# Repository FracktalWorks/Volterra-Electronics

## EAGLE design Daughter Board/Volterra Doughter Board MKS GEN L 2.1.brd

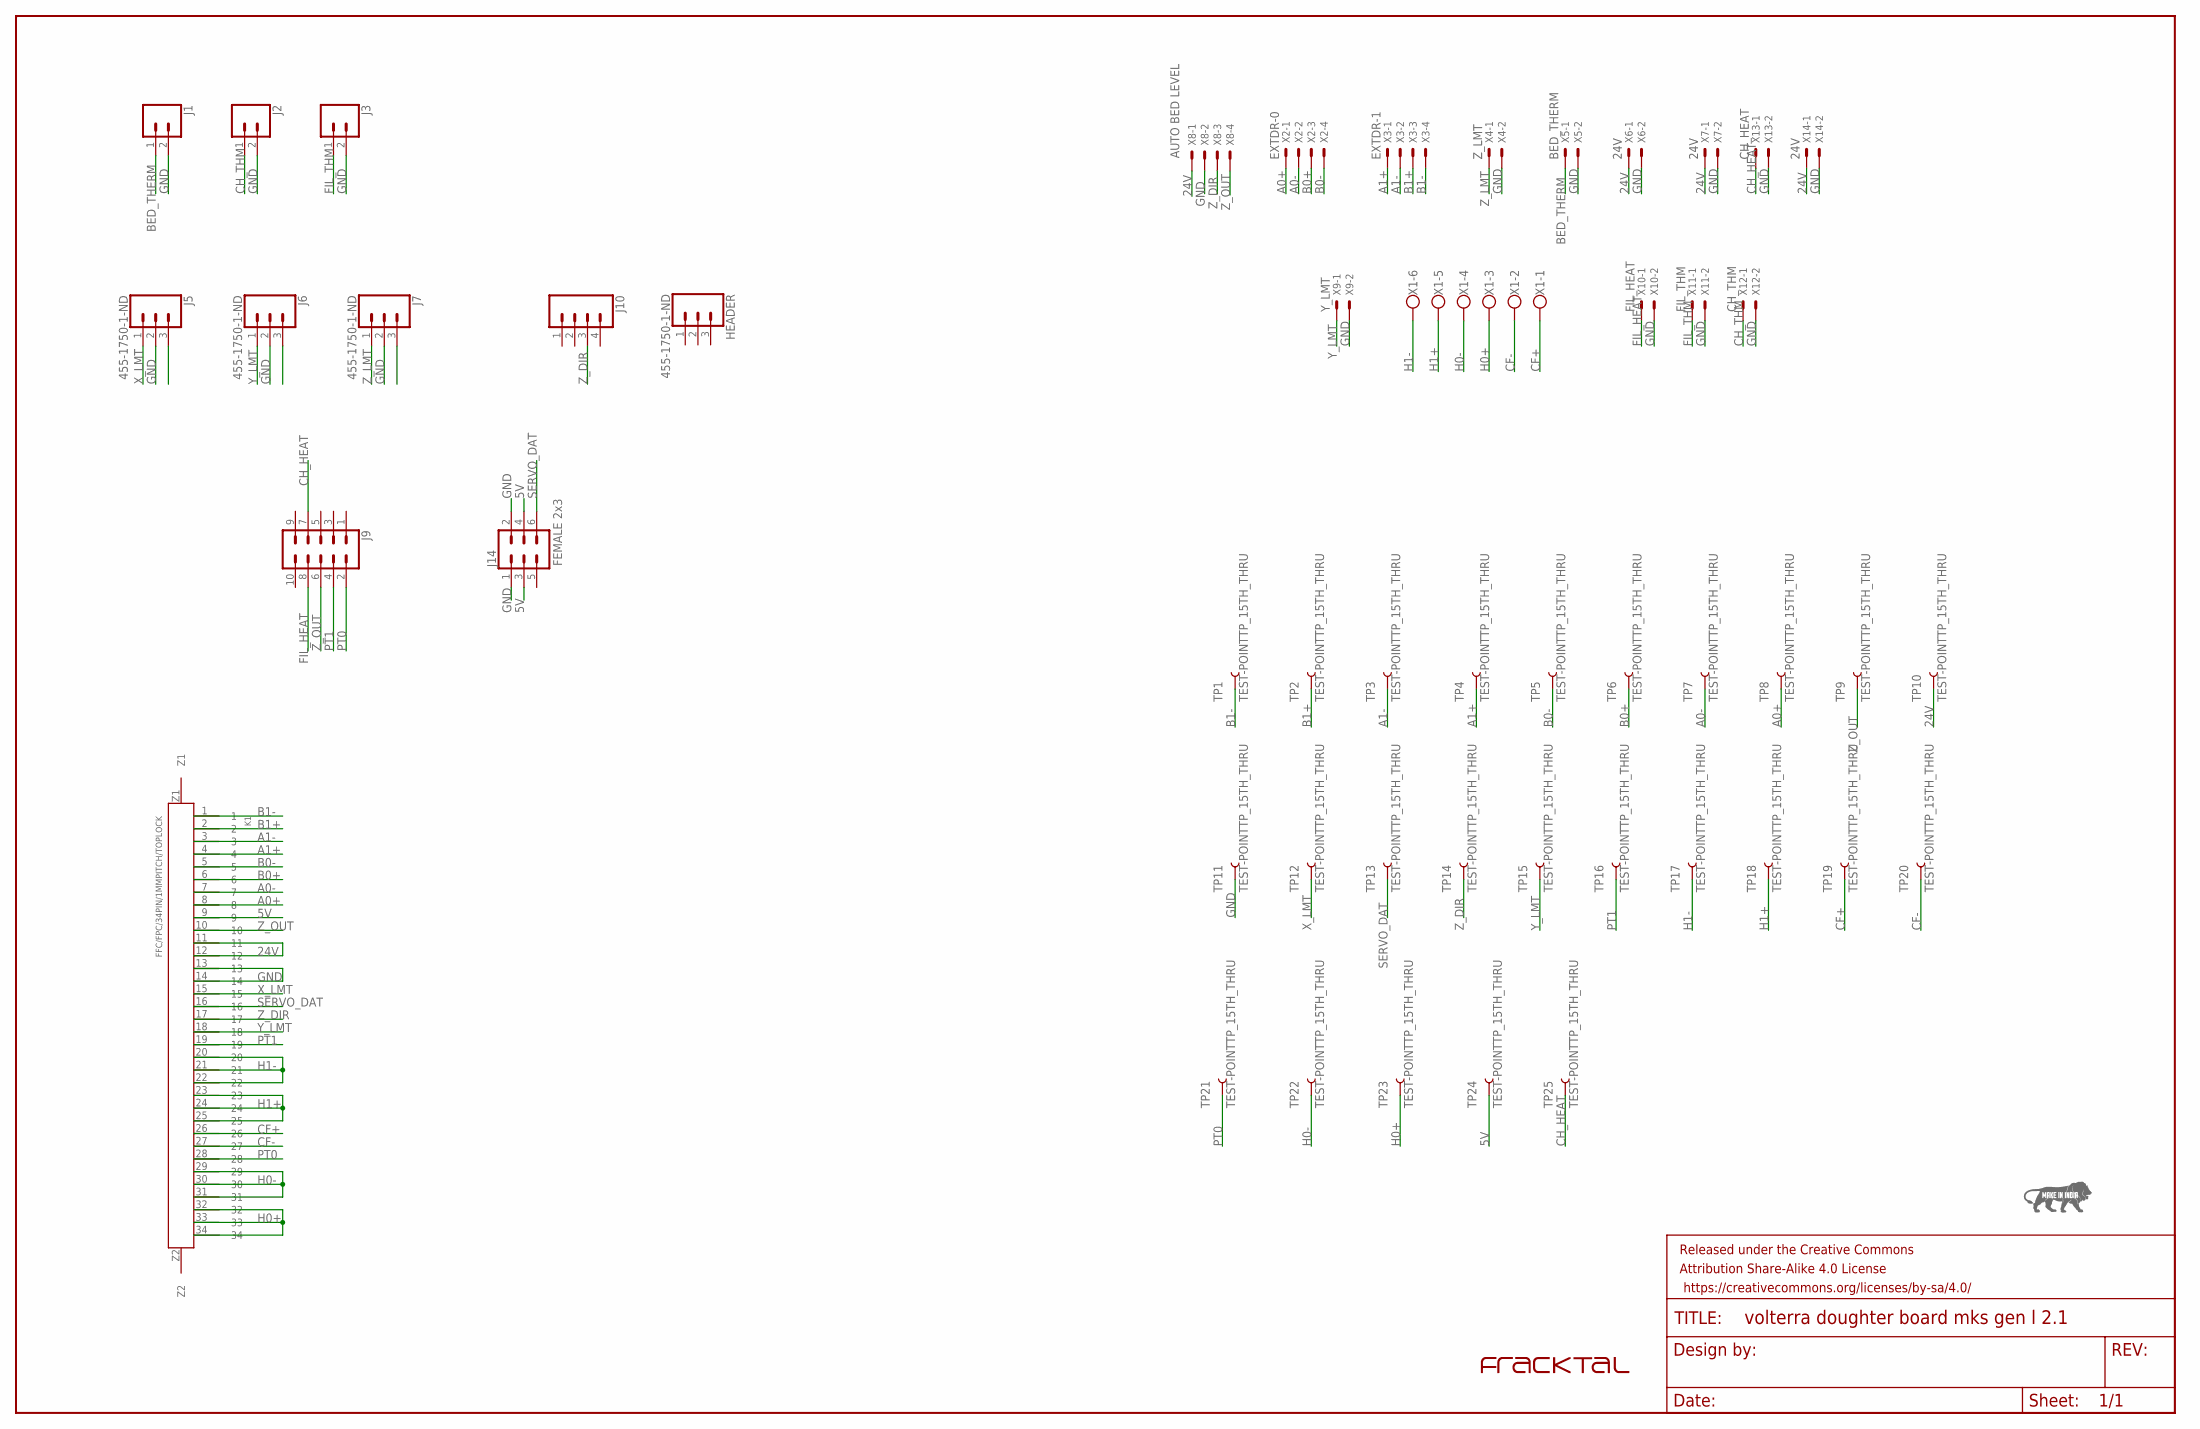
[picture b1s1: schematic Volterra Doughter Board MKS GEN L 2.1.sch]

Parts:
FRAME1: FRAME-LEDGER; CREATIVE_COMMONS
HEADER: 455-1750-1-ND; 1X03
J1, J2, J3: CONN_02; 1X02
J5, J6, J7: 455-1750-1-ND; 1X03
J9: CONN_05X2PTH; 2X5
J10: CONN_04; 1X04
J14: FEMALE 2x3; 2X3
K1: FFC/FPC/34PIN/1MMPITCH/TOPLOCK; 34PIN/1MMPITCH/FFC/FPC
TP1, TP2, TP3, TP4, TP5, TP6, TP7, TP8, TP9, TP10, TP11, TP12, TP13, TP14, TP15, TP16, TP17, TP18, TP19, TP20, TP21, TP22, TP23, TP24, TP25: TEST-POINTTP_15TH_THRU; TP_15TH
U$1: FRACKTALLOGO
U$2: MAKEININDIA
X1: W237-6
X2: EXTDR-0; JST-XH-04-PACKAGE-LONG-PAD
X3: EXTDR-1; JST-XH-04-PACKAGE-LONG-PAD
X4: Z_LMT; JST-XH-02-PACKAGE-LONG-PAD
X5: BED_THERM; JST-XH-02-PACKAGE-LONG-PAD
X6, X7, X14: 24V; JST-XH-02-PACKAGE-LONG-PAD
X8: AUTO BED LEVELING; JST-XH-04-PACKAGE-LONG-PAD
X9: Y_LMT; JST-XH-02-PACKAGE-LONG-PAD
X10: FIL_HEAT; JST-XH-02-PACKAGE-LONG-PAD
X11: FIL_THM; JST-XH-02-PACKAGE-LONG-PAD
X12: CH_THM; JST-XH-02-PACKAGE-LONG-PAD
X13: CH_HEAT; JST-XH-02-PACKAGE-LONG-PAD

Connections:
5V: J14.3, J14.4, K1.9, TP24.P$1
24V: K1.11, K1.12, TP10.P$1, X6.1, X7.1, X8.1, X14.1
A0+: K1.8, TP8.P$1, X2.1
A0-: K1.7, TP7.P$1, X2.2
A1+: K1.4, TP4.P$1, X3.1
A1-: K1.3, TP3.P$1, X3.2
B0+: K1.6, TP6.P$1, X2.3
B0-: K1.5, TP5.P$1, X2.4
B1+: K1.2, TP2.P$1, X3.3
B1-: K1.1, TP1.P$1, X3.4
BED_THERM: J1.1, X5.1
CF+: K1.26, TP19.P$1, X1.1
CF-: K1.27, TP20.P$1, X1.2
CH_HEAT: J9.7, TP25.P$1, X13.1
CH_THM: J2.1, X12.1
FIL_HEAT: J9.8, X10.1
FIL_THM: J3.1, X11.1
GND: J1.2, J2.2, J3.2, J5.2, J6.2, J7.2, J14.1, J14.2, K1.13, K1.14, TP11.P$1, X4.2, X5.2, X6.2, X7.2, X8.2, X9.2, X10.2, X11.2, X12.2, X13.2, X14.2
H0+: K1.32, K1.33, K1.34, TP23.P$1, X1.3
H0-: K1.29, K1.30, K1.31, TP22.P$1, X1.4
H1+: K1.23, K1.24, K1.25, TP18.P$1, X1.5
H1-: K1.20, K1.21, K1.22, TP17.P$1, X1.6
PT0: J9.2, K1.28, TP21.P$1
PT1: J9.4, K1.19, TP16.P$1
SERVO_DAT: J14.6, K1.16, TP13.P$1
X_LMT: J5.1, K1.15, TP12.P$1
Y_LMT: J6.1, K1.18, TP15.P$1, X9.1
Z_DIR: J10.3, K1.17, TP14.P$1, X8.3
Z_LMT: J7.1, X4.1
Z_OUT: J9.6, K1.10, TP9.P$1, X8.4

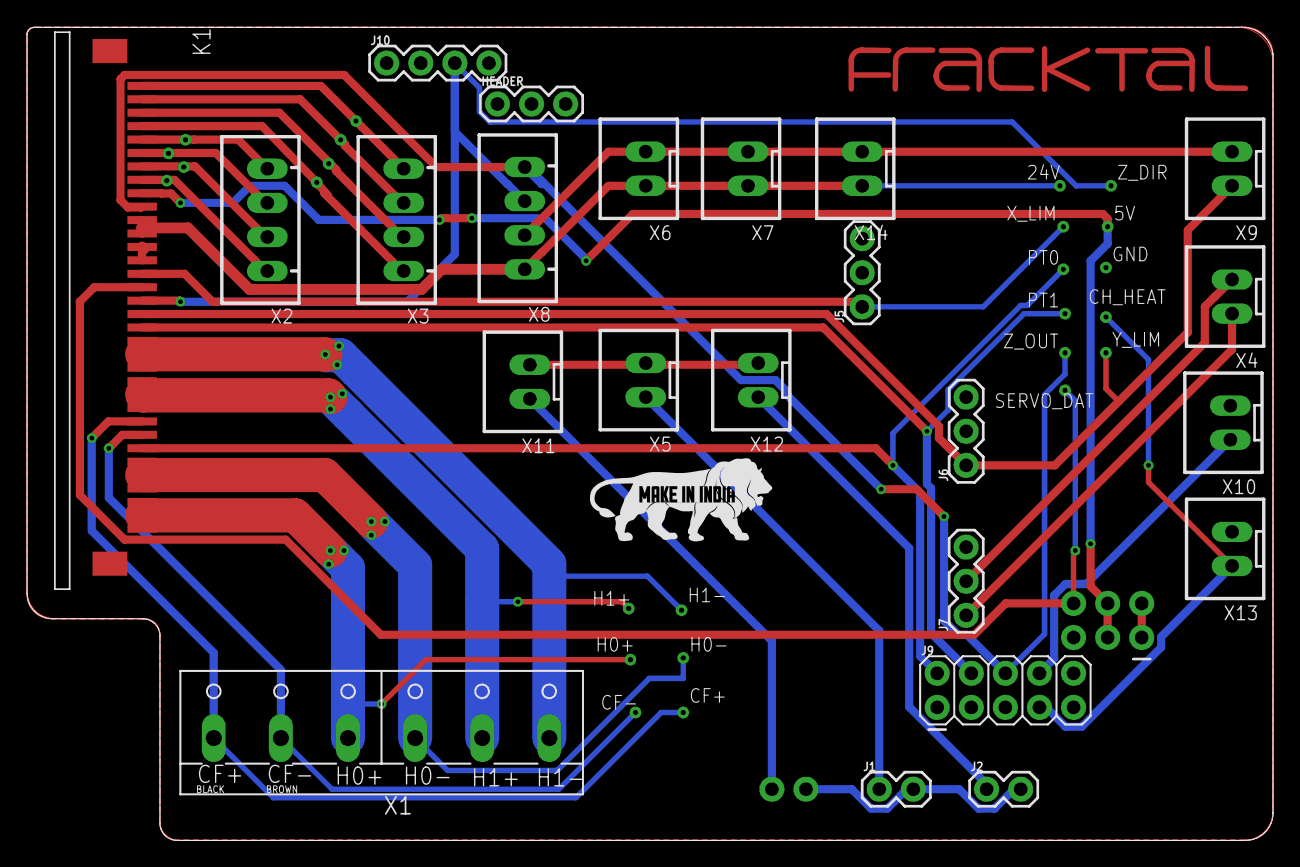
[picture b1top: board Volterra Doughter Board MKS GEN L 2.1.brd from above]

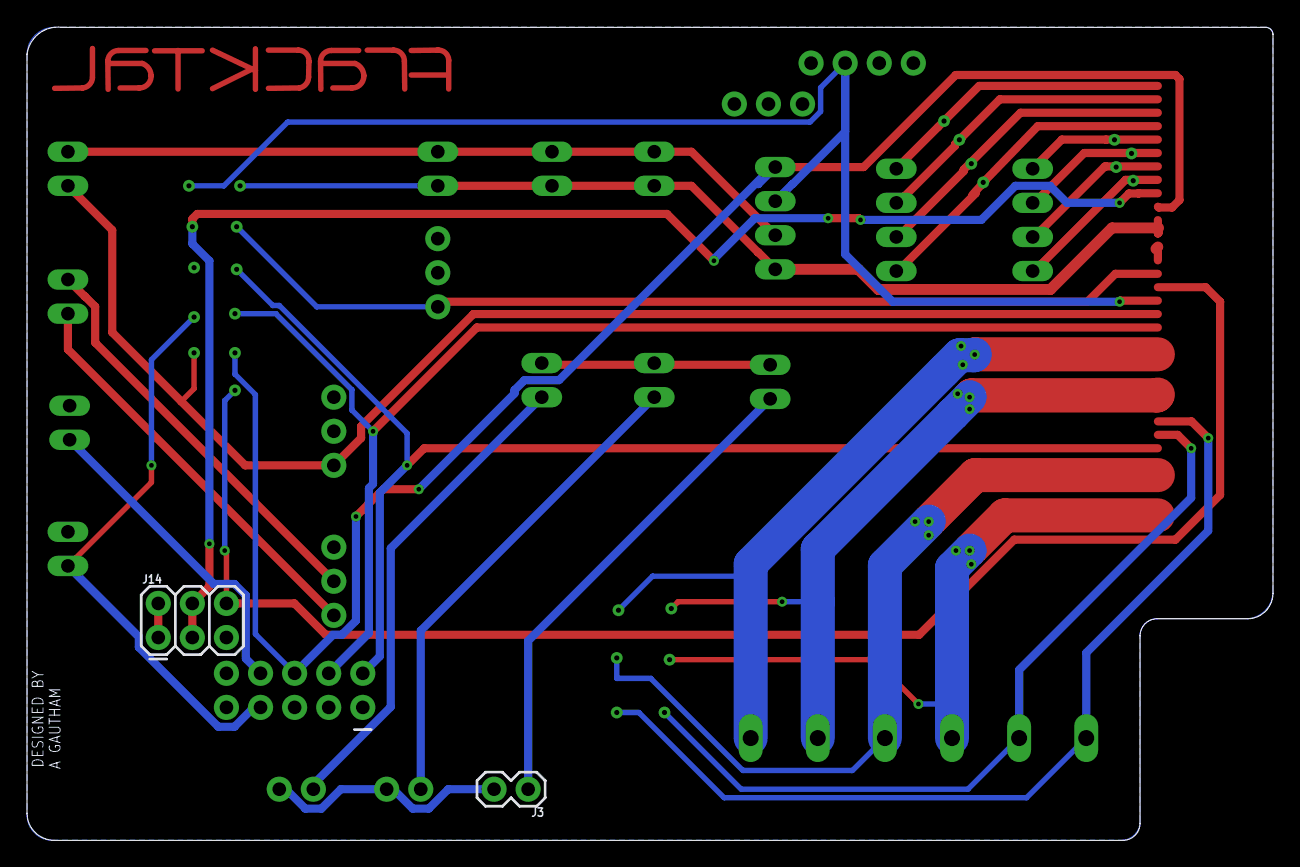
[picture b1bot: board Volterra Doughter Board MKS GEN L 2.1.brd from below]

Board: 2 copper layers, 92.8 x 60.6 mm, 53 parts (3 on the bottom side), 30 nets.

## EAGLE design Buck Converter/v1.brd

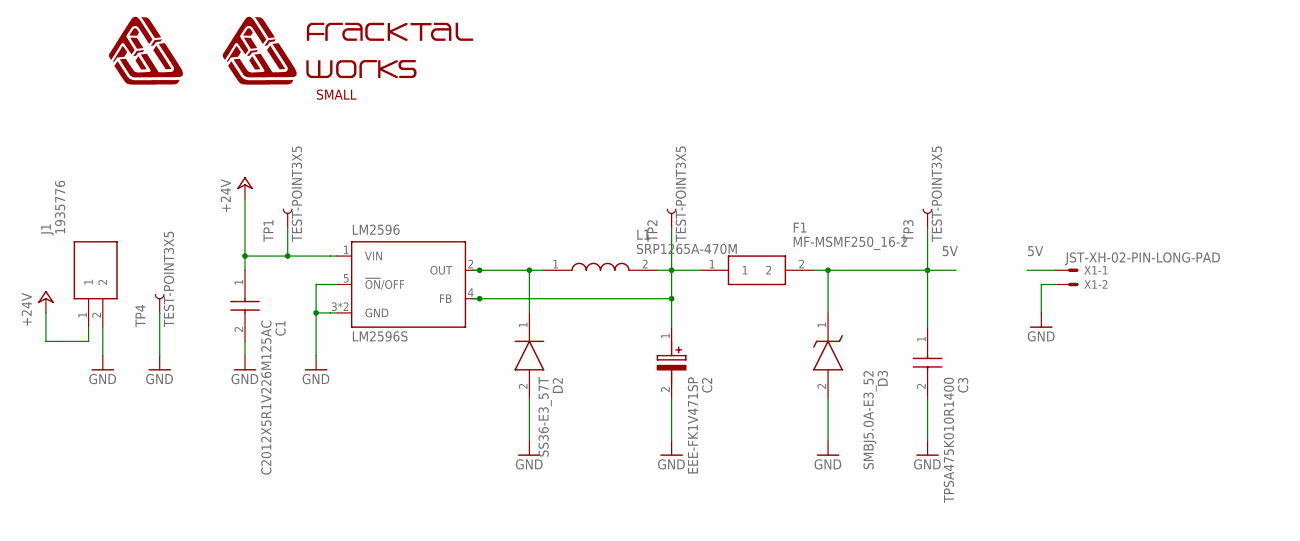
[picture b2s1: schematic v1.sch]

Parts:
C1: C2012X5R1V226M125AC; CAPC2012X145N
C2: EEE-FK1V471SP; CAPAE1030X1050N
C3: TPSA475K010R1400; CAPPM3216X180N
D2: SS36-E3_57T; DIOM7959X262N
D3: SMBJ5.0A-E3_52; DIOM5436X244N
F1: MF-MSMF250_16-2; FUSC4632X160N
J1: 1935776; SHDR2W110P0X500_1X2_1000X900X1
L1: SRP1265A-470M; SRP1265A
LM2596: LM2596S; LM2596_TO263-5
TP1, TP2, TP3, TP4: TEST-POINT3X5; PAD.03X.05
U$1: FWLOGO
U$2: FWLOGO_TEXT_SMALL
X1: JST-XH-02-PIN-LONG-PAD; JST-XH-02-PACKAGE-LONG-PAD

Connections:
5V: C3.1, D3.1 (K), F1.2, TP3.P$1, X1.1
+24V: C1.1, J1.1, LM2596.1 (VIN), TP1.P$1
GND: C1.2, C2.2 (-), C3.2, D2.2 (A), D3.2 (A), J1.2, LM2596.3 (GND), LM2596.5 (!ON!/OFF), LM2596.6 (GND), TP4.P$1, X1.2
unnamed: D2.1 (K), L1.1, LM2596.2 (OUT)
unnamed: C2.1 (+), F1.1, L1.2, LM2596.4 (FB), TP2.P$1

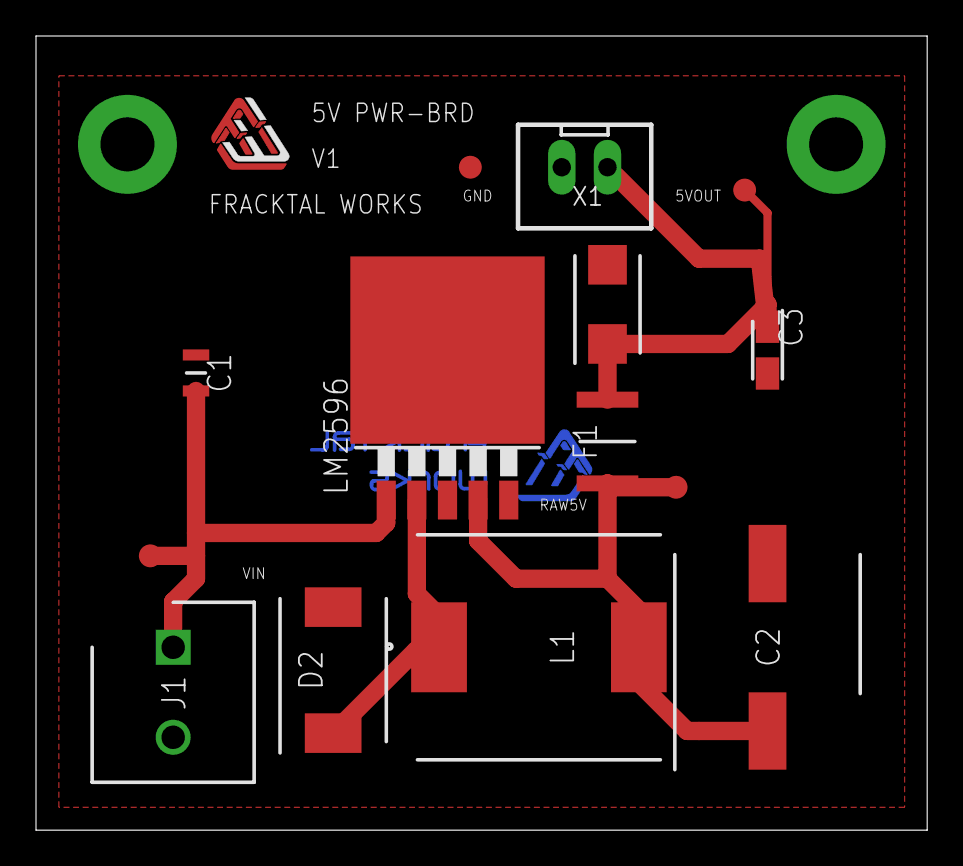
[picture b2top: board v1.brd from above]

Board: 2 copper layers, 49.5 x 44.1 mm, 16 parts (1 on the bottom side), 5 nets.

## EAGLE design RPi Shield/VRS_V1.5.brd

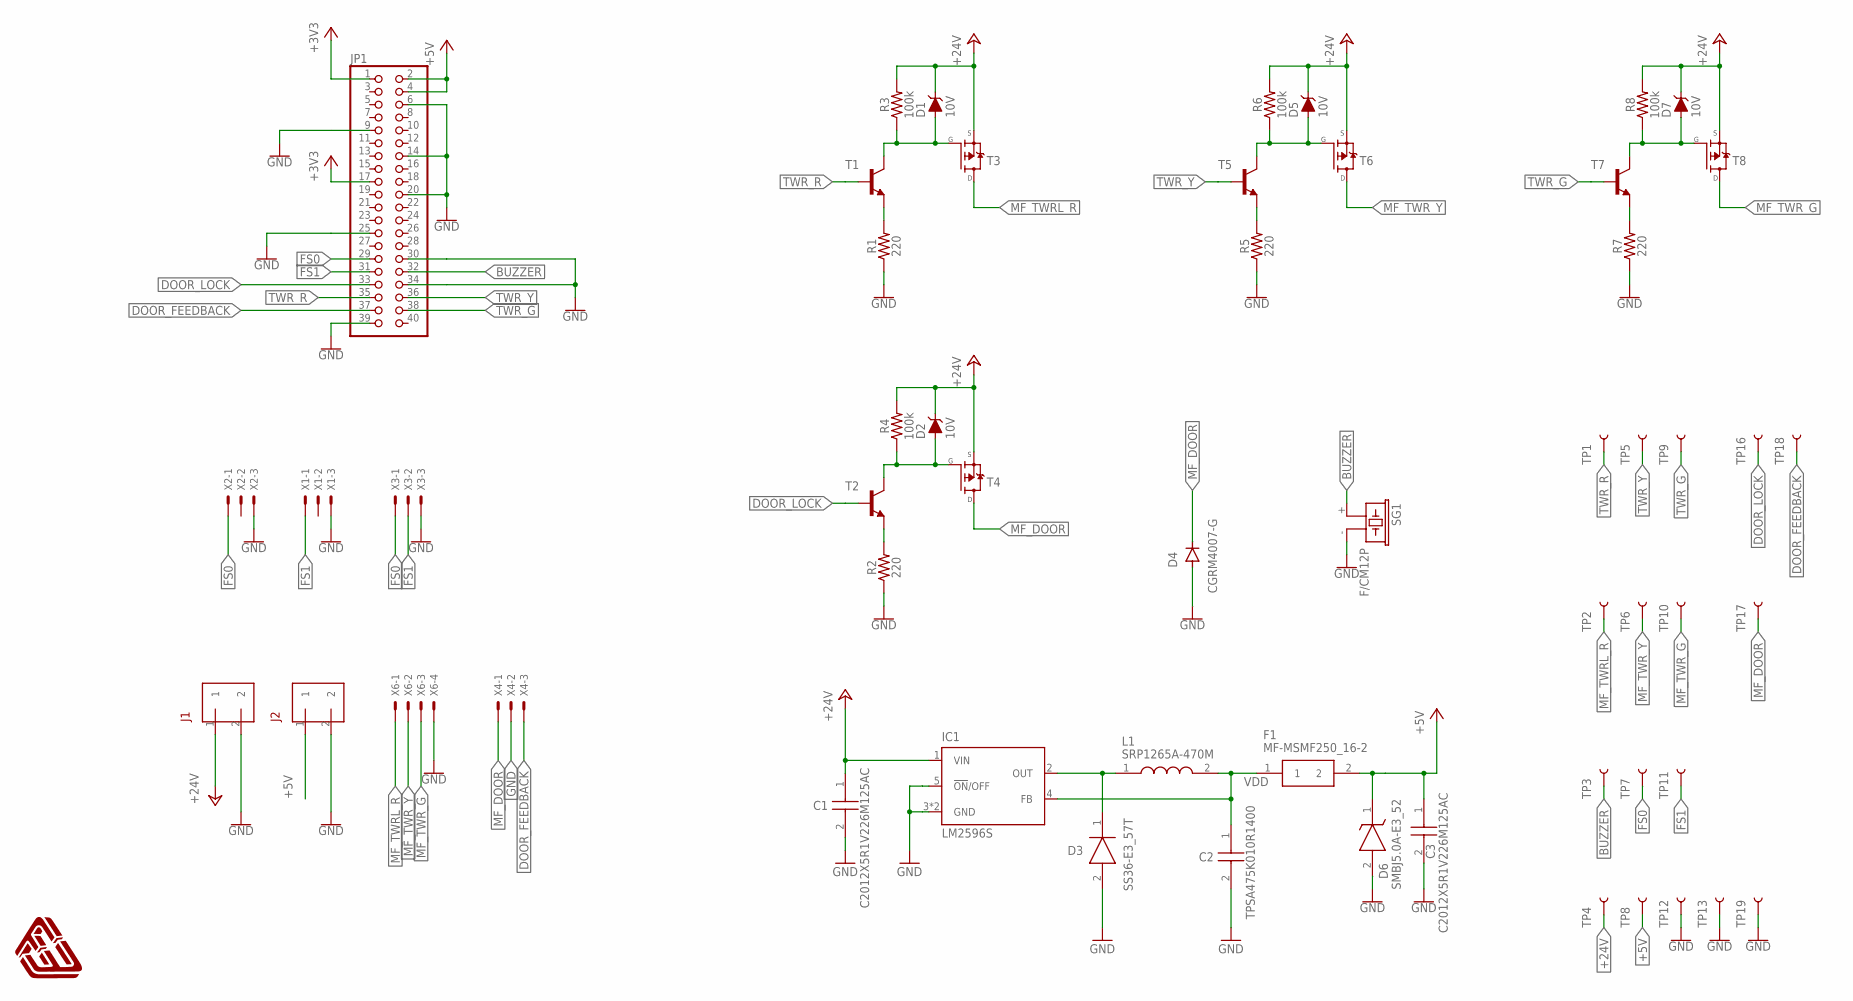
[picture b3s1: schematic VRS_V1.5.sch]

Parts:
C1, C3: C2012X5R1V226M125AC; CAPC2012X145N
C2: TPSA475K010R1400; CAPPM3216X180N
D1, D2, D5, D7: 10V; PANASONIC_SMINI2-F5-B
D3: SS36-E3_57T; DIOM7959X262N
D4: CGRM4007-G; SOD-123_MINI-SMA
D6: SMBJ5.0A-E3_52; DIOM5436X244N
F1: MF-MSMF250_16-2; FUSC4632X160N
FWLOGO_1: FWLOGO
IC1: LM2596S; LM2596_TO263-5
J1, J2: TERMINALBLOCK/TOYO/2PIN/5MMPITCH
JP1: RASPBERRYPI_3B_GPIO
L1: SRP1265A-470M; SRP1265A
R1, R2, R5, R7: 220; 0603
R3, R4, R6, R8: 100k; 0603
SG1: F/CM12P
T1, T2, T5, T7: MMBT3904LT1-NPN-SOT23-BEC; SOT23-BEC
T3, T4, T6, T8: MOSFET_P_SOT223; MOSFET_SOT223
TP1, TP2, TP3, TP4, TP5, TP6, TP7, TP8, TP9, TP10, TP11, TP12, TP13, TP16, TP17, TP18, TP19: TEST-POINT3X5; PAD.03X.05
X1: FS1; JST-XH-03-PACKAGE-LONG-PAD
X2: FS0; JST-XH-03-PACKAGE-LONG-PAD
X3: ENCODER; JST-XH-03-PACKAGE-LONG-PAD
X4: DOOR LOCK; JST-XH-03-PACKAGE-LONG-PAD
X6: TOWER LIGHT; JST-XH-04-PACKAGE-LONG-PAD

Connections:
+3V3: JP1.1, JP1.17
+5V: C3.1, D6.1 (K), F1.2, J2.1, JP1.2, JP1.4, TP8.P$1
+24V: C1.1, D1.C, D2.C, D5.C, D7.C, IC1.1 (VIN), J1.1, R3.2, R4.2, R6.2, R8.2, T3.3 (S), T4.3 (S), T6.3 (S), T8.3 (S), TP4.P$1
BUZZER: JP1.32, SG1.+ (1), TP3.P$1
DOOR_FEEDBACK: JP1.37, TP18.P$1, X4.3
DOOR_LOCK: JP1.33, T2.B, TP16.P$1
FS0: JP1.29, TP7.P$1, X2.1, X3.1
FS1: JP1.31, TP11.P$1, X1.1, X3.2
GND: C1.2, C2.2, C3.2, D3.2 (A), D4.A, D6.2 (A), IC1.3 (GND), IC1.5 (!ON!/OFF), IC1.6 (GND), J1.2, J2.2, JP1.6, JP1.9, JP1.14, JP1.20, JP1.25, JP1.30, JP1.34, JP1.39, R1.1, R2.1, R5.1, R7.1, SG1.- (2), TP12.P$1, TP13.P$1, TP19.P$1, X1.3, X2.3, X3.3, X4.2, X6.4
MF_DOOR: D4.C, T4.2 (D), T4.4 (D), TP17.P$1, X4.1
MF_TWRL_R: T3.2 (D), T3.4 (D), TP2.P$1, X6.1
MF_TWR_G: T8.2 (D), T8.4 (D), TP10.P$1, X6.3
MF_TWR_Y: T6.2 (D), T6.4 (D), TP6.P$1, X6.2
unnamed: R1.2, T1.E
unnamed: D3.1 (K), IC1.2 (OUT), L1.1
unnamed: D5.A, R6.1, T5.C, T6.1 (G)
unnamed: D1.A, R3.1, T1.C, T3.1 (G)
unnamed: R5.2, T5.E
unnamed: D7.A, R8.1, T7.C, T8.1 (G)
unnamed: R7.2, T7.E
unnamed: D2.A, R4.1, T2.C, T4.1 (G)
unnamed: R2.2, T2.E
TWR_G: JP1.38, T7.B, TP9.P$1
TWR_R: JP1.35, T1.B, TP1.P$1
TWR_Y: JP1.36, T5.B, TP5.P$1
VDD: C2.1, F1.1, IC1.4 (FB), L1.2

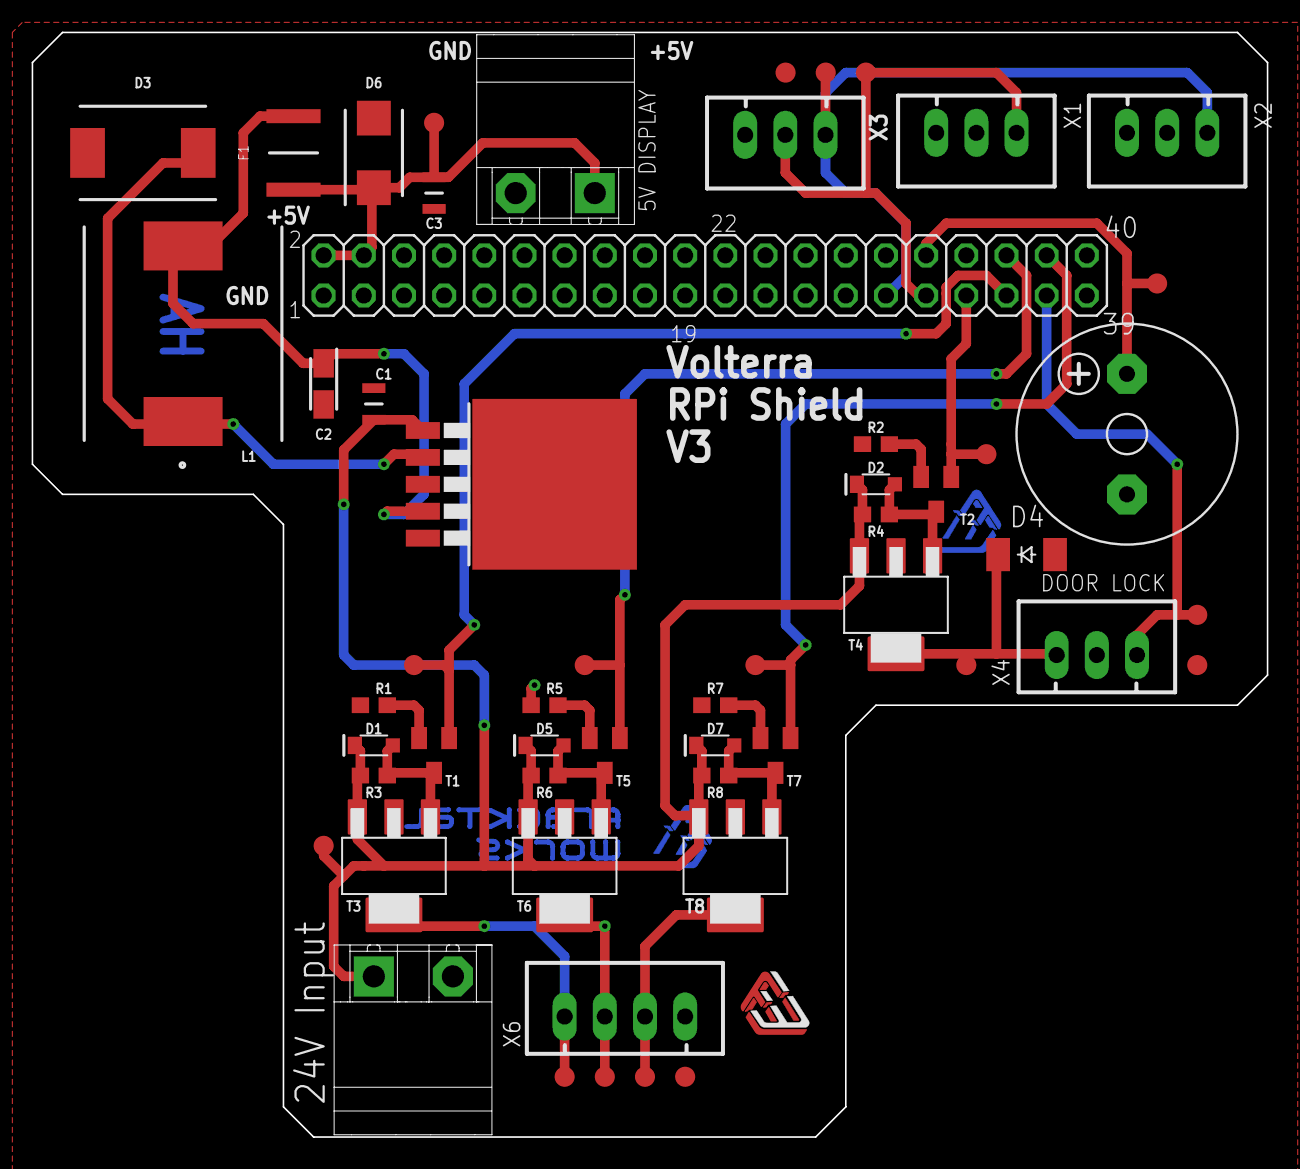
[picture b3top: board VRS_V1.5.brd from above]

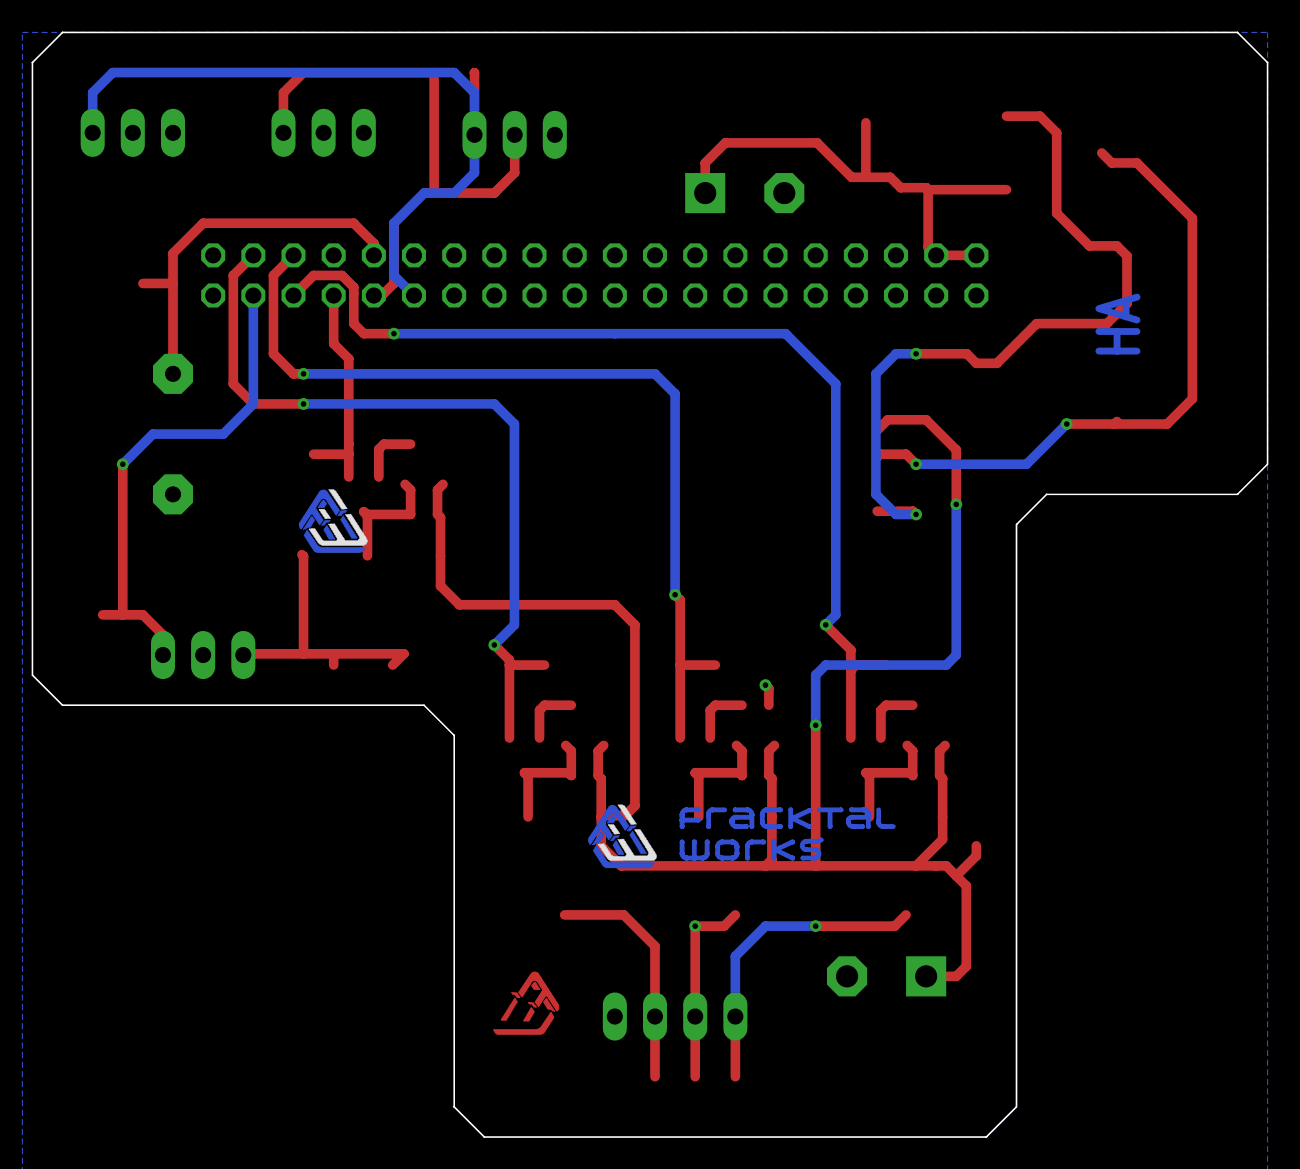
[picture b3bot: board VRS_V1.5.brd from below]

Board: 2 copper layers, 78.1 x 69.8 mm, 59 parts (3 on the bottom side), 26 nets.

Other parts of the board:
M_HA_3: HA_MARK
U$2: FWLOGO_TEXT_SMALL
U$3: FWLOGO

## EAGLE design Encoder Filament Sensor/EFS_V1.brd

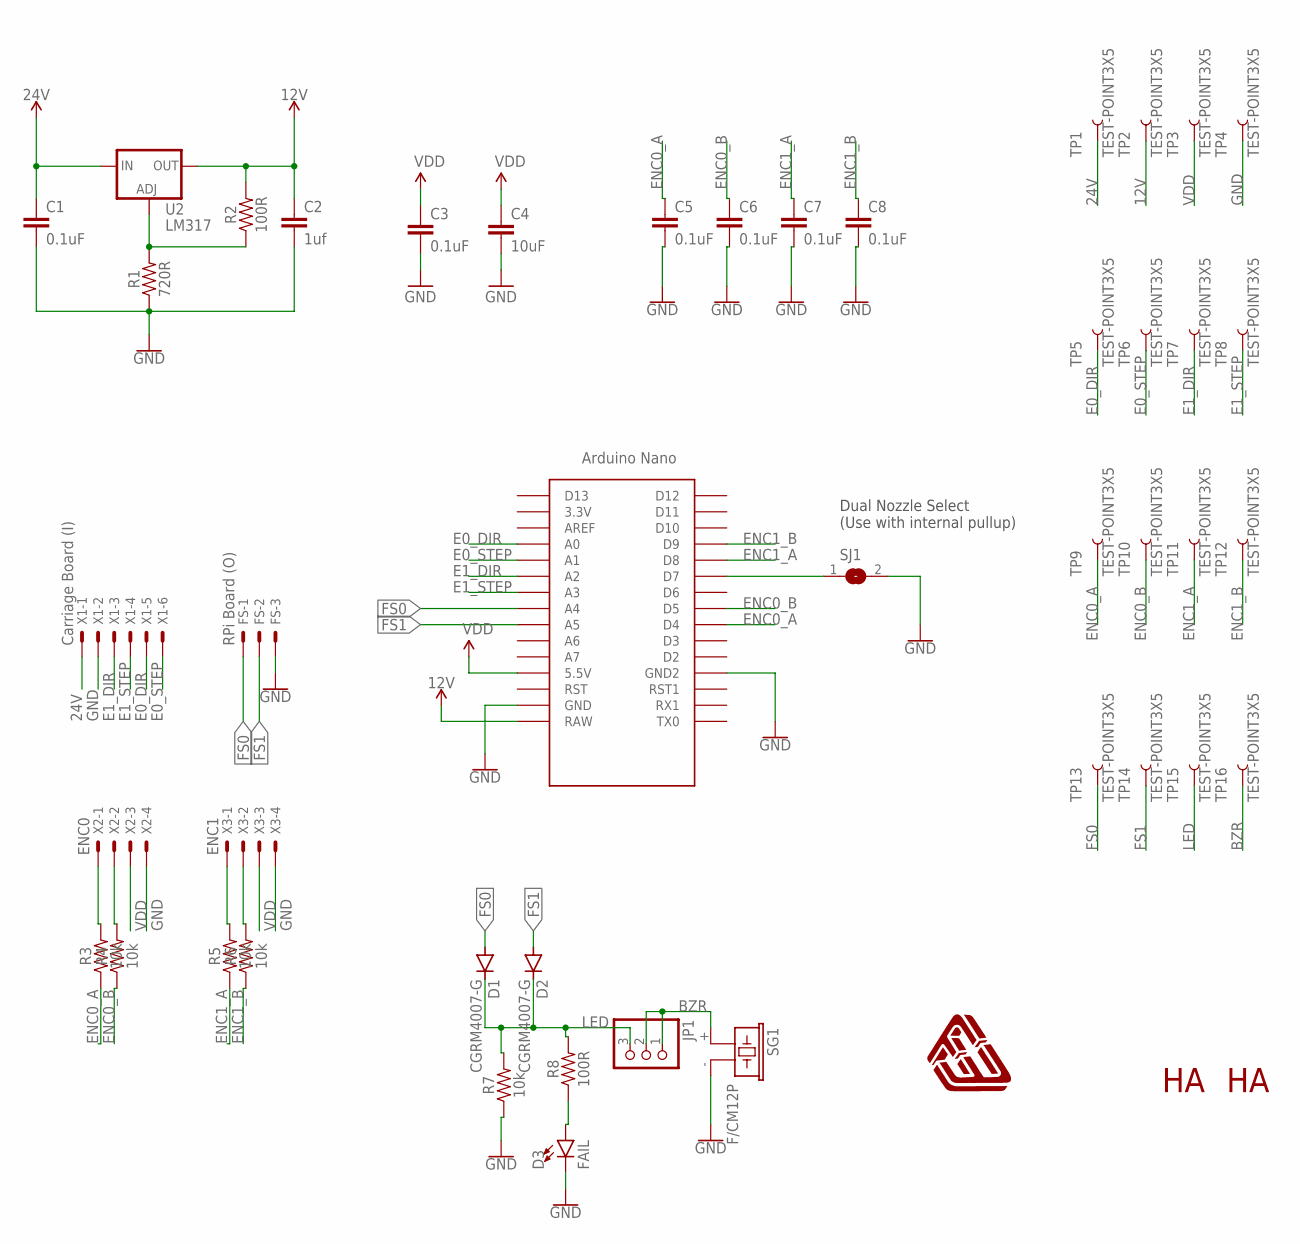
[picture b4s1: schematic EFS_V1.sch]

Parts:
C1, C5, C6, C7, C8: 0.1uF; 0603
C2: 1uf; 0603
C3: 0.1uF; 0603-CAP
C4: 10uF; 1210
D1, D2: CGRM4007-G; SOD-123_MINI-SMA
D3: FAIL; LED_3MM
FS: RPi Board (O); JST-XH-03-PACKAGE-LONG-PAD
JP1: PINHD-1X3; 1X03
M_HA_1, M_HA_2: HA_MARK
R1: 720R; 0603
R2, R8: 100R; 0603
R3, R4, R5, R6, R7: 10k; 0603
SG1: F/CM12P
SJ1: SJW
TP1, TP2, TP3, TP4, TP5, TP6, TP7, TP8, TP9, TP10, TP11, TP12, TP13, TP14, TP15, TP16: TEST-POINT3X5; PAD.03X.05
U2: LM317; SOT223
U$1: NANO
U$2: FWLOGO
X1: Carriage Board (I); JST-XH-06-PACKAGE-LONG-PAD
X2: ENC0; JST-XH-04-PACKAGE-LONG-PAD
X3: ENC1; JST-XH-04-PACKAGE-LONG-PAD

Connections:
12V: C2.1, R2.2, TP2.P$1, U2.2 (OUT), U$1.RAW
24V: C1.1, TP1.P$1, U2.3 (IN), X1.1
ADJ1: R1.2, R2.1, U2.1 (ADJ)
BZR: JP1.1, JP1.2, SG1.+ (1), TP16.P$1
E0_DIR: TP5.P$1, U$1.A0, X1.5
E0_STEP: TP6.P$1, U$1.A1, X1.6
E1_DIR: TP7.P$1, U$1.A2, X1.3
E1_STEP: TP8.P$1, U$1.A3, X1.4
ENC0_A: C5.1, R3.1, TP9.P$1, U$1.D4
ENC0_B: C6.1, R4.1, TP10.P$1, U$1.D5
ENC1_A: C7.1, R5.1, TP11.P$1, U$1.D8
ENC1_B: C8.1, R6.1, TP12.P$1, U$1.D9
FS0: D1.A, FS.1, TP13.P$1, U$1.A4
FS1: D2.A, FS.2, TP14.P$1, U$1.A5
GND: C1.2, C2.2, C3.2, C4.2, C5.2, C6.2, C7.2, C8.2, D3.K (C), FS.3, R1.1, R7.1, SG1.- (2), SJ1.2, TP4.P$1, U$1.GND, U$1.GND1 (GND2), X1.2, X2.4, X3.4
LED: D1.C, D2.C, JP1.3, R7.2, R8.2, TP15.P$1
unnamed: R3.2, X2.1
unnamed: R4.2, X2.2
unnamed: R5.2, X3.1
unnamed: R6.2, X3.2
unnamed: SJ1.1, U$1.D7
unnamed: D3.A, R8.1
VDD: C3.1, C4.1, TP3.P$1, U$1.5V (5.5V), X2.3, X3.3

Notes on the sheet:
Dual Nozzle Select (Use with internal pullup)

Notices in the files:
parts and their libraries:
SparkFun-Connectors: Licensing: Creative Commons ShareAlike 4.0 International - https://creativecommons.org/licenses/by-sa/4.0
SparkFun-Aesthetics: Released under the Creative Commons Attribution Share-Alike 4.0 License
SparkFun-Aesthetics: https://creativecommons.org/licenses/by-sa/4.0
